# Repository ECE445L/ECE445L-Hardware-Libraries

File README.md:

# ECE445L-Hardware-Libraries
A common repository template for using ECE 445L hardware libraries and provided files.

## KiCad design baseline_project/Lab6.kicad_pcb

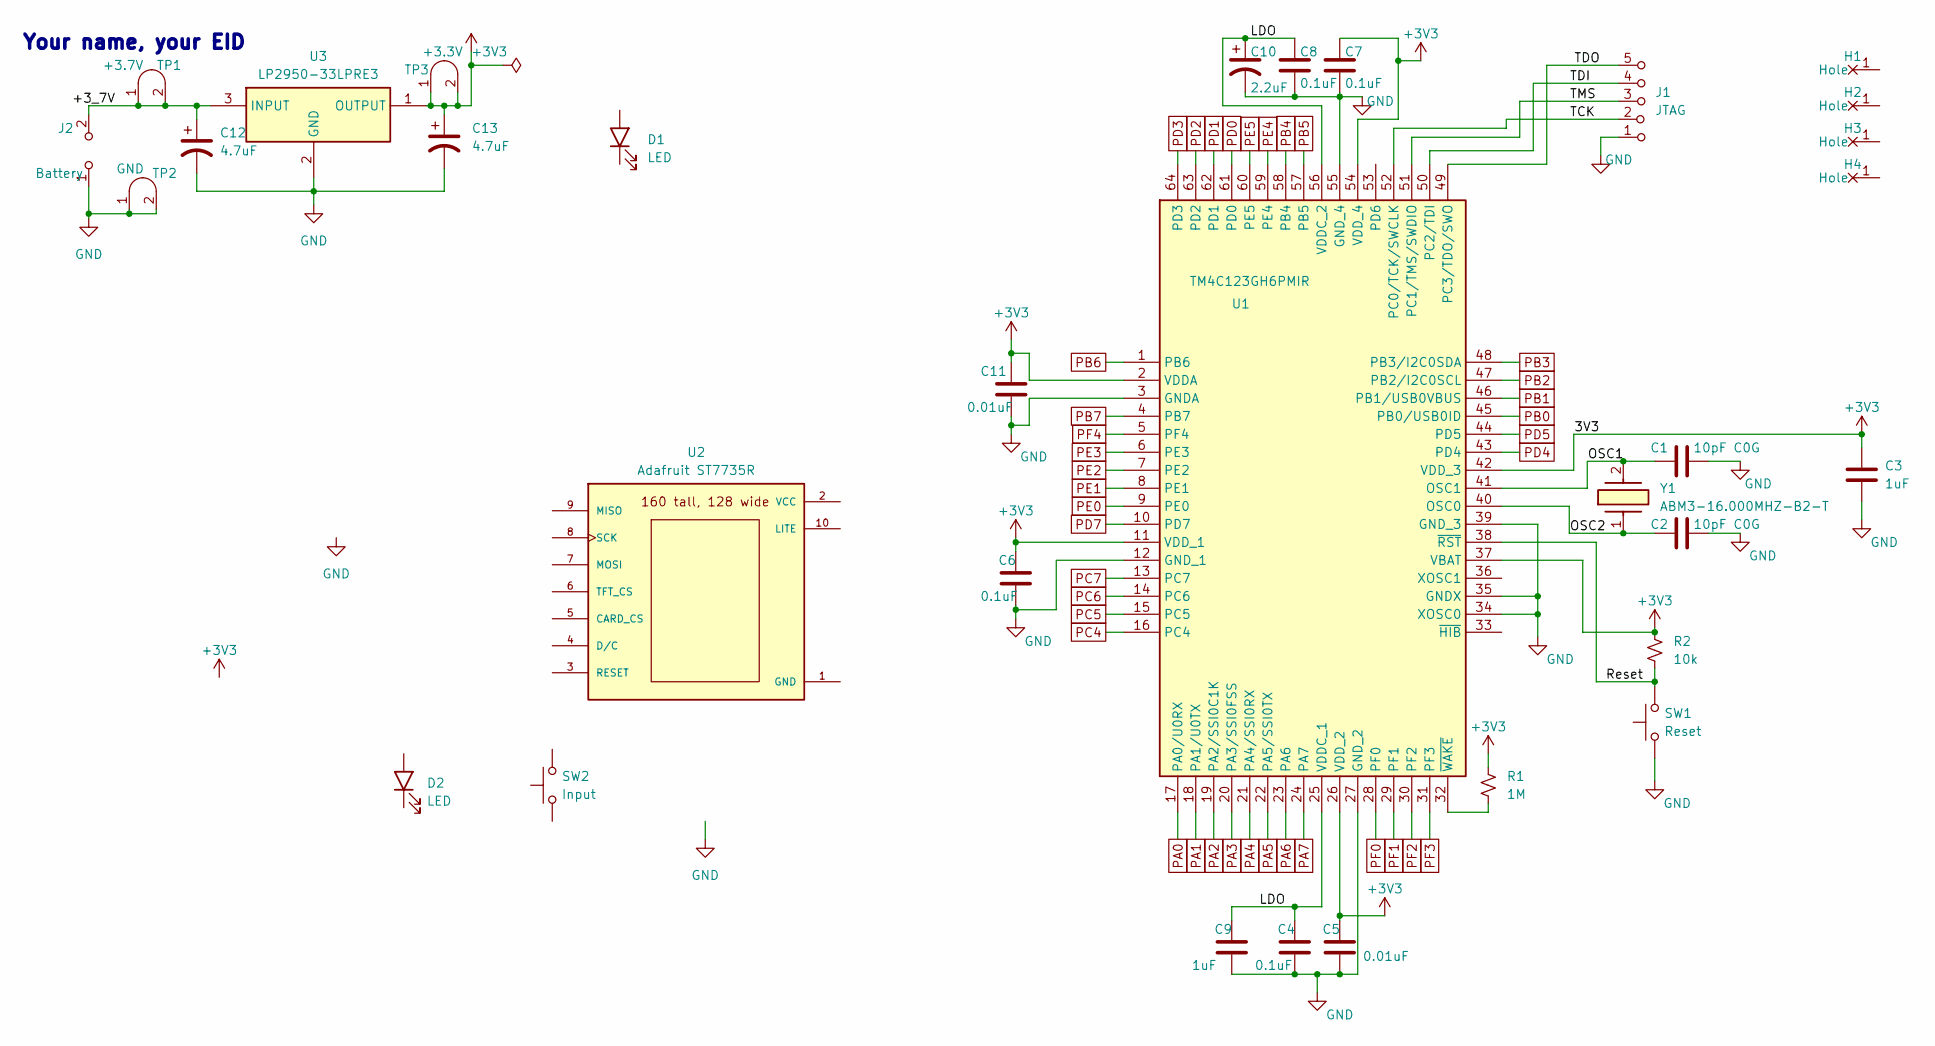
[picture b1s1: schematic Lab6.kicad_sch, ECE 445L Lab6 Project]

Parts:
C1, C2: 10pF C0G; C_Axial_200mil
C3, C9: 1uF; C_Axial_200mil
C4, C6, C7, C8: 0.1uF; C_Axial_200mil
C5, C11: 0.01uF; C_Axial_200mil
C10: 2.2uF; CP_Radial_Tantal200mil
C12, C13: 4.7uF; CP_Radial_Tantal200mil
D1, D2: LED; LED_D5.0mm
H1, H2, H3, H4: MountingHole_4_40
J1: JTAG; PinHeader_1x05_P2.54mm_Vertical
J2: Battery; PinHeader_1x02_P2.54mm_Vertical
R1: 1M; R_Axial_DIN0204_L3.6mm_D1.6mm_P7.62mm_Horizontal
R2: 10k; R_Axial_DIN0204_L3.6mm_D1.6mm_P7.62mm_Horizontal
SW1: Reset; SW_PUSH_6mm
SW2: Input; SW_PUSH_6mm
TP1: +3.7V; Testpoint_1x02_P2.54mm
TP2: GND; Testpoint_1x02_P2.54mm
TP3: +3.3V; Testpoint_1x02_P2.54mm
U1: TM4C123GH6PMIR; QFP50P1200X1200X160-64N; Mouser Part Number 595-TM4C123GH6PMIR
U2: Adafruit ST7735R; adafruit_st7735r2
U3: LP2950-33LPRE3; TL431CLPM; Mouser Part Number 595-LP2950-33LPRE3
Y1: ABM3-16.000MHZ-B2-T; ABM3; Mouser Part Number 815-ABM3-16-B2-T

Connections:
+3V3: C3.1, C5.1, C6.1, C7.1, C11.1, C13.1, R1.1, R2.1, TP3.1 (A), TP3.2 (B), U1.2 (VDDA), U1.11 (VDD_1), U1.26 (VDD_2), U1.37 (VBAT), U1.42 (VDD_3), U1.54 (VDD_4), U3.1 (OUTPUT)
/+3_7V: C12.1, J2.2 (B), TP1.1 (A), TP1.2 (B), U3.3 (INPUT)
/LDO: C4.1, C8.1, C9.1, C10.1, U1.25 (VDDC_1), U1.56 (VDDC_2)
/OSC1: C1.1, U1.41 (OSC1), Y1.2
/OSC2: C2.1, U1.40 (OSC0), Y1.1
/Reset: R2.2, SW1.2, U1.38 (~RST)
/TCK: J1.2 (B), U1.52 (PC0/TCK/SWCLK)
/TDI: J1.4 (C), U1.50 (PC2/TDI)
/TDO: J1.5 (C), U1.49 (PC3/TDO/SWO)
/TMS: J1.3 (C), U1.51 (PC1/TMS/SWDIO)
GND: C1.2, C2.2, C3.2, C4.2, C5.2, C6.2, C7.2, C8.2, C9.2, C10.2, C11.2, C12.2, C13.2, J1.1 (A), J2.1 (A), SW1.1, TP2.1 (A), TP2.2 (B), U1.3 (GNDA), U1.12 (GND_1), U1.27 (GND_2), U1.34 (XOSC0), U1.35 (GNDX), U1.39 (GND_3), U1.55 (GND_4), U3.2 (GND)
unnamed: R1.2, U1.32 (~WAKE)
PA0: U1.17 (PA0/U0RX)
PA1: U1.18 (PA1/U0TX)
PA2: U1.19 (PA2/SSI0C1K)
PA3: U1.20 (PA3/SSI0FSS)
PA4: U1.21 (PA4/SSI0RX)
PA5: U1.22 (PA5/SSI0TX)
PA6: U1.23 (PA6)
PA7: U1.24 (PA7)
PB0: U1.45 (PB0/USB0ID)
PB1: U1.46 (PB1/USB0VBUS)
PB2: U1.47 (PB2/I2C0SCL)
PB3: U1.48 (PB3/I2C0SDA)
PB4: U1.58 (PB4)
PB5: U1.57 (PB5)
PB6: U1.1 (PB6)
PB7: U1.4 (PB7)
PC4: U1.16 (PC4)
PC5: U1.15 (PC5)
PC6: U1.14 (PC6)
PC7: U1.13 (PC7)
PD0: U1.61 (PD0)
PD1: U1.62 (PD1)
PD2: U1.63 (PD2)
PD3: U1.64 (PD3)
PD4: U1.43 (PD4)
PD5: U1.44 (PD5)
PD7: U1.10 (PD7)
PE0: U1.9 (PE0)
PE1: U1.8 (PE1)
PE2: U1.7 (PE2)
PE3: U1.6 (PE3)
PE4: U1.59 (PE4)
PE5: U1.60 (PE5)
PF0: U1.28 (PF0)
PF1: U1.29 (PF1)
PF2: U1.30 (PF2)
PF3: U1.31 (PF3)
PF4: U1.5 (PF4)

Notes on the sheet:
Your name, your EID

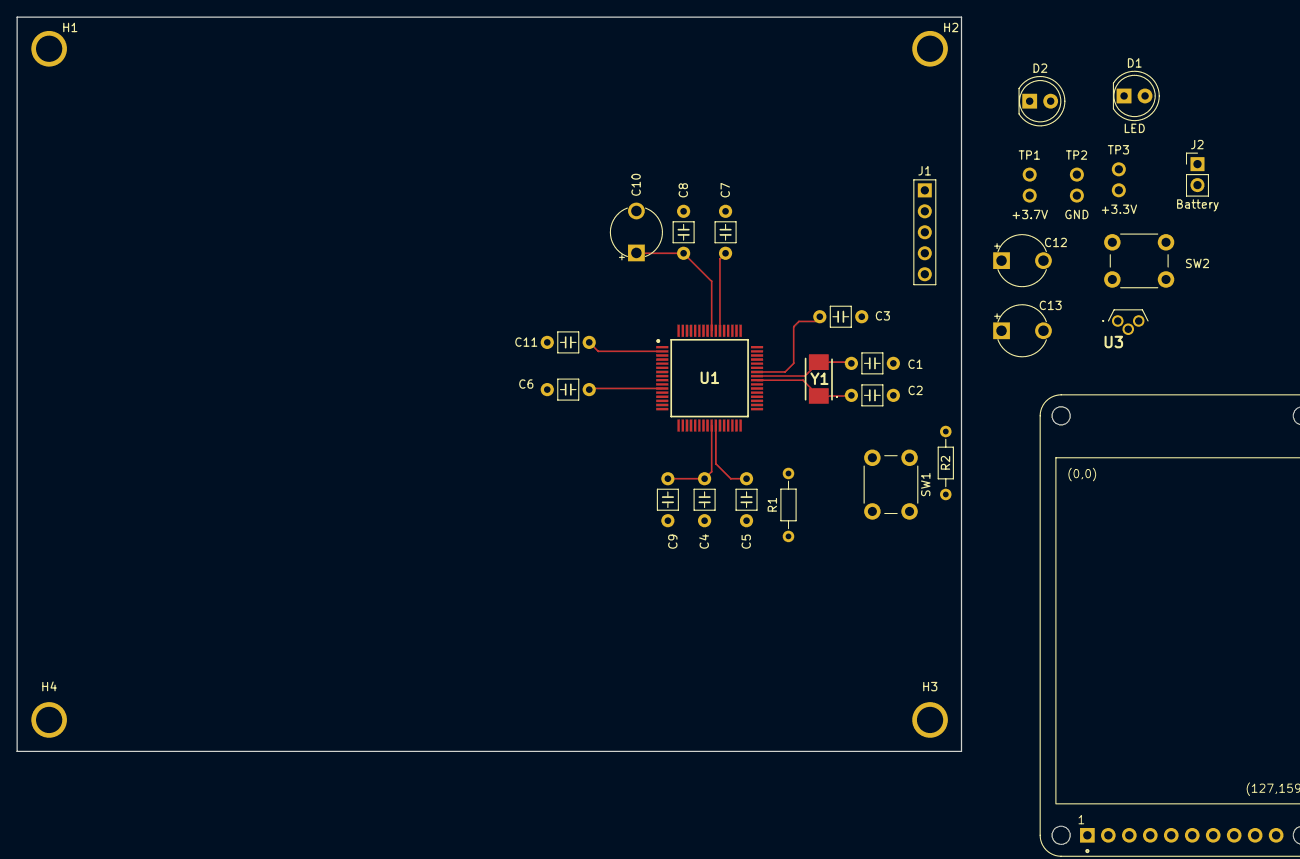
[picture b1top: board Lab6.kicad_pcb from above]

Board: 2 copper layers, 114.4 x 88.9 mm, 32 parts (0 on the bottom side), 12 nets.

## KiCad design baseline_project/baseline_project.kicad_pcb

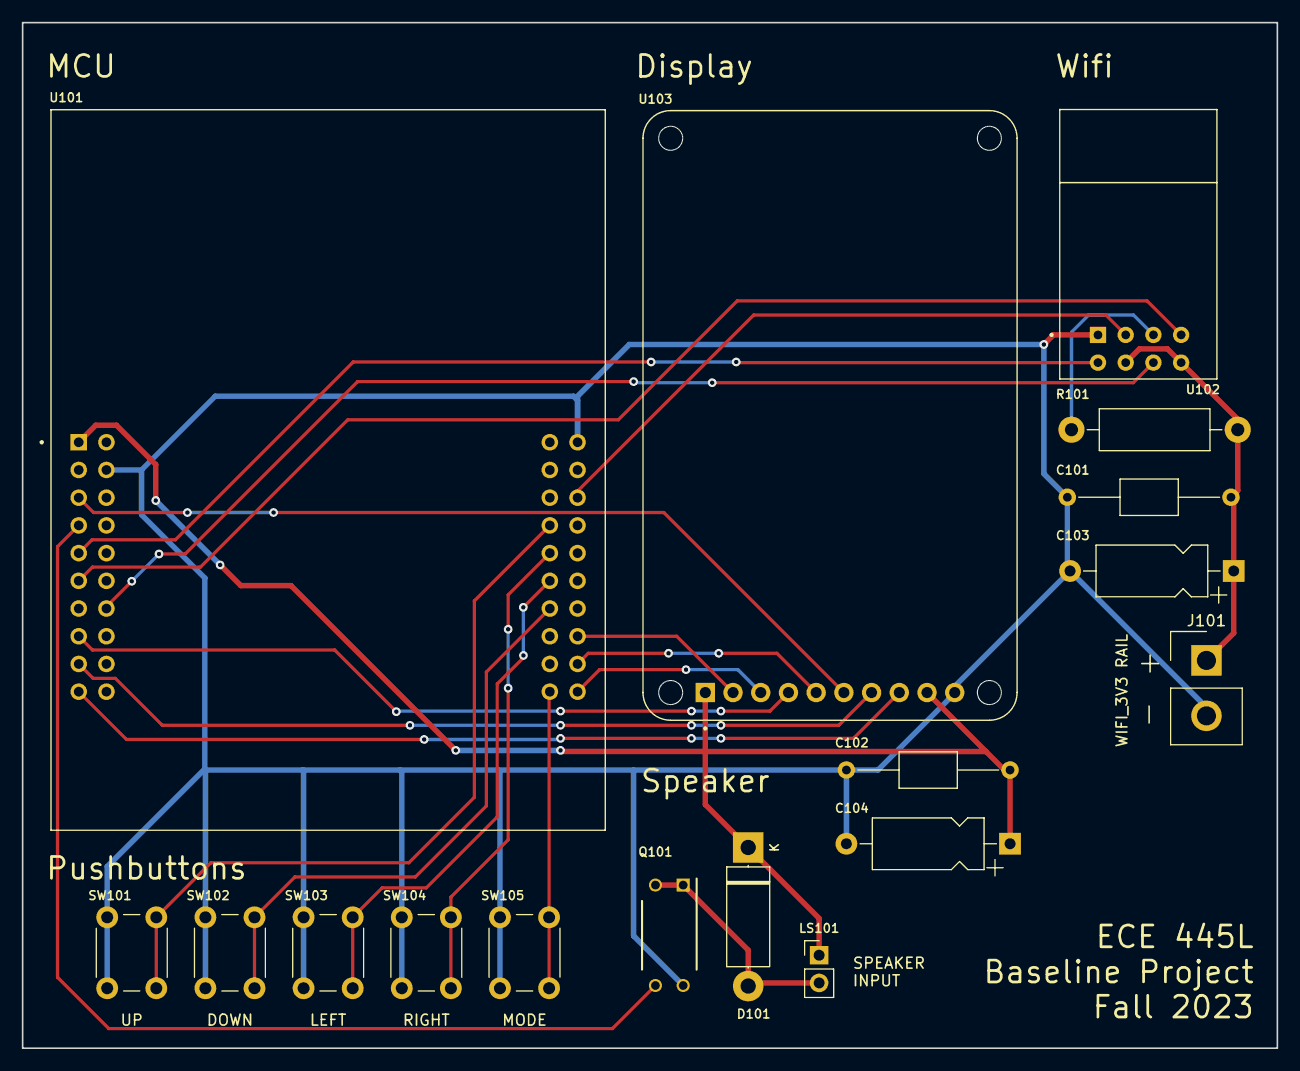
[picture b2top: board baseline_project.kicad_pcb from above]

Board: 2 copper layers, 115.0 x 94.0 mm, 17 parts (0 on the bottom side), 22 nets.

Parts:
C101, C102: 100nF; C_Axial_L5.1mm_D3.1mm_P15.00mm_Horizontal
C103, C104: 4.7uF; CP_Axial_L10.0mm_D4.5mm_P15.00mm_Horizontal
D101: 1V0; D_5W_P12.70mm_Horizontal
J101: EXT_3V3; Samtec_HPM-02-01-x-S_Straight_1x02_Pitch5.08mm
LS101: Speaker; PinHeader_1x02_P2.54mm_Vertical
Q101: IRLD024PBF; vishay_IRLD024PBF
R101: 10k; R_Axial_DIN0411_L9.9mm_D3.6mm_P15.24mm_Horizontal
SW101: UP; SW_PUSH_6mm
SW102: DOWN; SW_PUSH_6mm
SW103: LEFT; SW_PUSH_6mm
SW104: RIGHT; SW_PUSH_6mm
SW105: MODE; SW_PUSH_6mm
U101: EK-TM4C123GXL; ti_EKTM4C123GXL
U102: ESP8266-01/ESP-01; ai_thinker_ESP8266_01
U103: Adafruit ST7735R; adafruit_st7735r

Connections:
+3V3: C102.1, C104.1, D101.1 (K), LS101.1, U101.J1_1 (+3.3V), U103.1 (LITE), U103.9 (VCC)
/SDC_CS: U101.J1_3 (PB0), U103.6 (CARD_CS)
/SPEAKER_GATE: Q101.2 (G), U101.J1_4 (PB1)
/SW_DOWN: SW102.2, U101.J4_7 (PC7)
/SW_LEFT: SW103.2, U101.J4_6 (PC6)
/SW_MODE: SW105.2, U101.J4_10 (PF4)
/SW_RIGHT: SW104.2, U101.J4_5 (PC5)
/SW_UP: SW101.2, U101.J4_4 (PC4)
/TFT_CS: U101.J2_9 (PA3), U103.5 (TFT_CS)
/TFT_D/C: U101.J1_9 (PA6), U103.7 (D/C)
/TFT_MISO: U101.J2_8 (PA4), U103.2 (MISO)
/TFT_MOSI: U101.J1_8 (PA5), U103.4 (MOSI)
/TFT_RST: U101.J1_10 (PA7), U103.8 (RESET)
/TFT_SCK: U101.J2_10 (PA2), U103.3 (SCK)
/WIFI_3V3: C101.1, C103.1, J101.1, R101.1, U102.6 (EN), U102.8 (VCC)
/WIFI_IO2: U101.J2_3 (PE0), U102.2 (IO2)
/WIFI_RXD: U101.J1_6 (PE5), U102.4 (RXD)
/WIFI_TXD: U101.J1_5 (PE4), U102.5 (TXD)
/~WIFI_RST: U101.J3_7 (PE1), U102.7 (~RST)
GND: C101.2, C102.2, C103.2, C104.2, J101.2, Q101.3 (S), SW101.1, SW102.1, SW103.1, SW104.1, SW105.1, U101.J2_1 (GND), U101.J3_2 (GND), U102.1 (GND), U103.10 (GND)
unnamed: D101.2 (A), LS101.2, Q101.1 (D)
unnamed: R101.2, U102.3 (IO0)

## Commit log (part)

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2023-01-10 restore to base hw files
2023-08-29 init commit for baseline project
2023-08-31 added parts for lab 5
2023-08-31 remove backups, update gitignore
2023-11-14 Added First Symbol for MSPM0
2023-11-14 Updated symbol name
2023-11-14 Added LQFP64, WIP Launchpad
2023-11-14 Added LP specific pins to symbol
2023-11-14 Added VSSOP WIP
2023-11-18 Added generic LQFP and VSSOP footprints
2023-12-11 Merging 319K parts
2023-12-11 More merging 319K
2023-12-12 and more merging
2024-01-14 update to KiCad
    1 by 4 header and LM4041
2024-02-20 Lab6 starter
    Just started, needs power, crystal and caps
2024-02-21 Lab6 starter version 2
    Needs some starter PCB place and trace
2024-02-21 Lab6 starter
    I am ready to release Lab6 starter and updated ECE445L library
2024-02-27 turn pot
    matches one in cabinet
2024-02-27 added PD6
    fixed ERC error with two +3V3 nets
2024-03-02 Fixed st7735 model
2024-04-10 organizational change
2024-08-07 KiCad starter files
2024-08-30 Valvano Dump
2025-02-10 Reorganized Files
2025-02-10 Align to grid
2025-02-10 Renamed projects
2025-02-10 Renamed lab6
2025-03-03 Add lab 7 files
2025-04-01 Add RSLKv2
2025-10-01 added LM4890 amp
2025-10-12 Swap TDI and TDO
2025-12-15 Clean up 3D models, used embedded model files, add models where missing. KiCad built-in models were used where possible, and if not possible, and embedded model was used
2026-01-08 change default ESP8266 footprint
2026-01-09 update all symbols and re-sync footprints in the KiCad projects
2026-03-06 MSPM0 Starter
2026-04-13 fix MSPM0 footprint
